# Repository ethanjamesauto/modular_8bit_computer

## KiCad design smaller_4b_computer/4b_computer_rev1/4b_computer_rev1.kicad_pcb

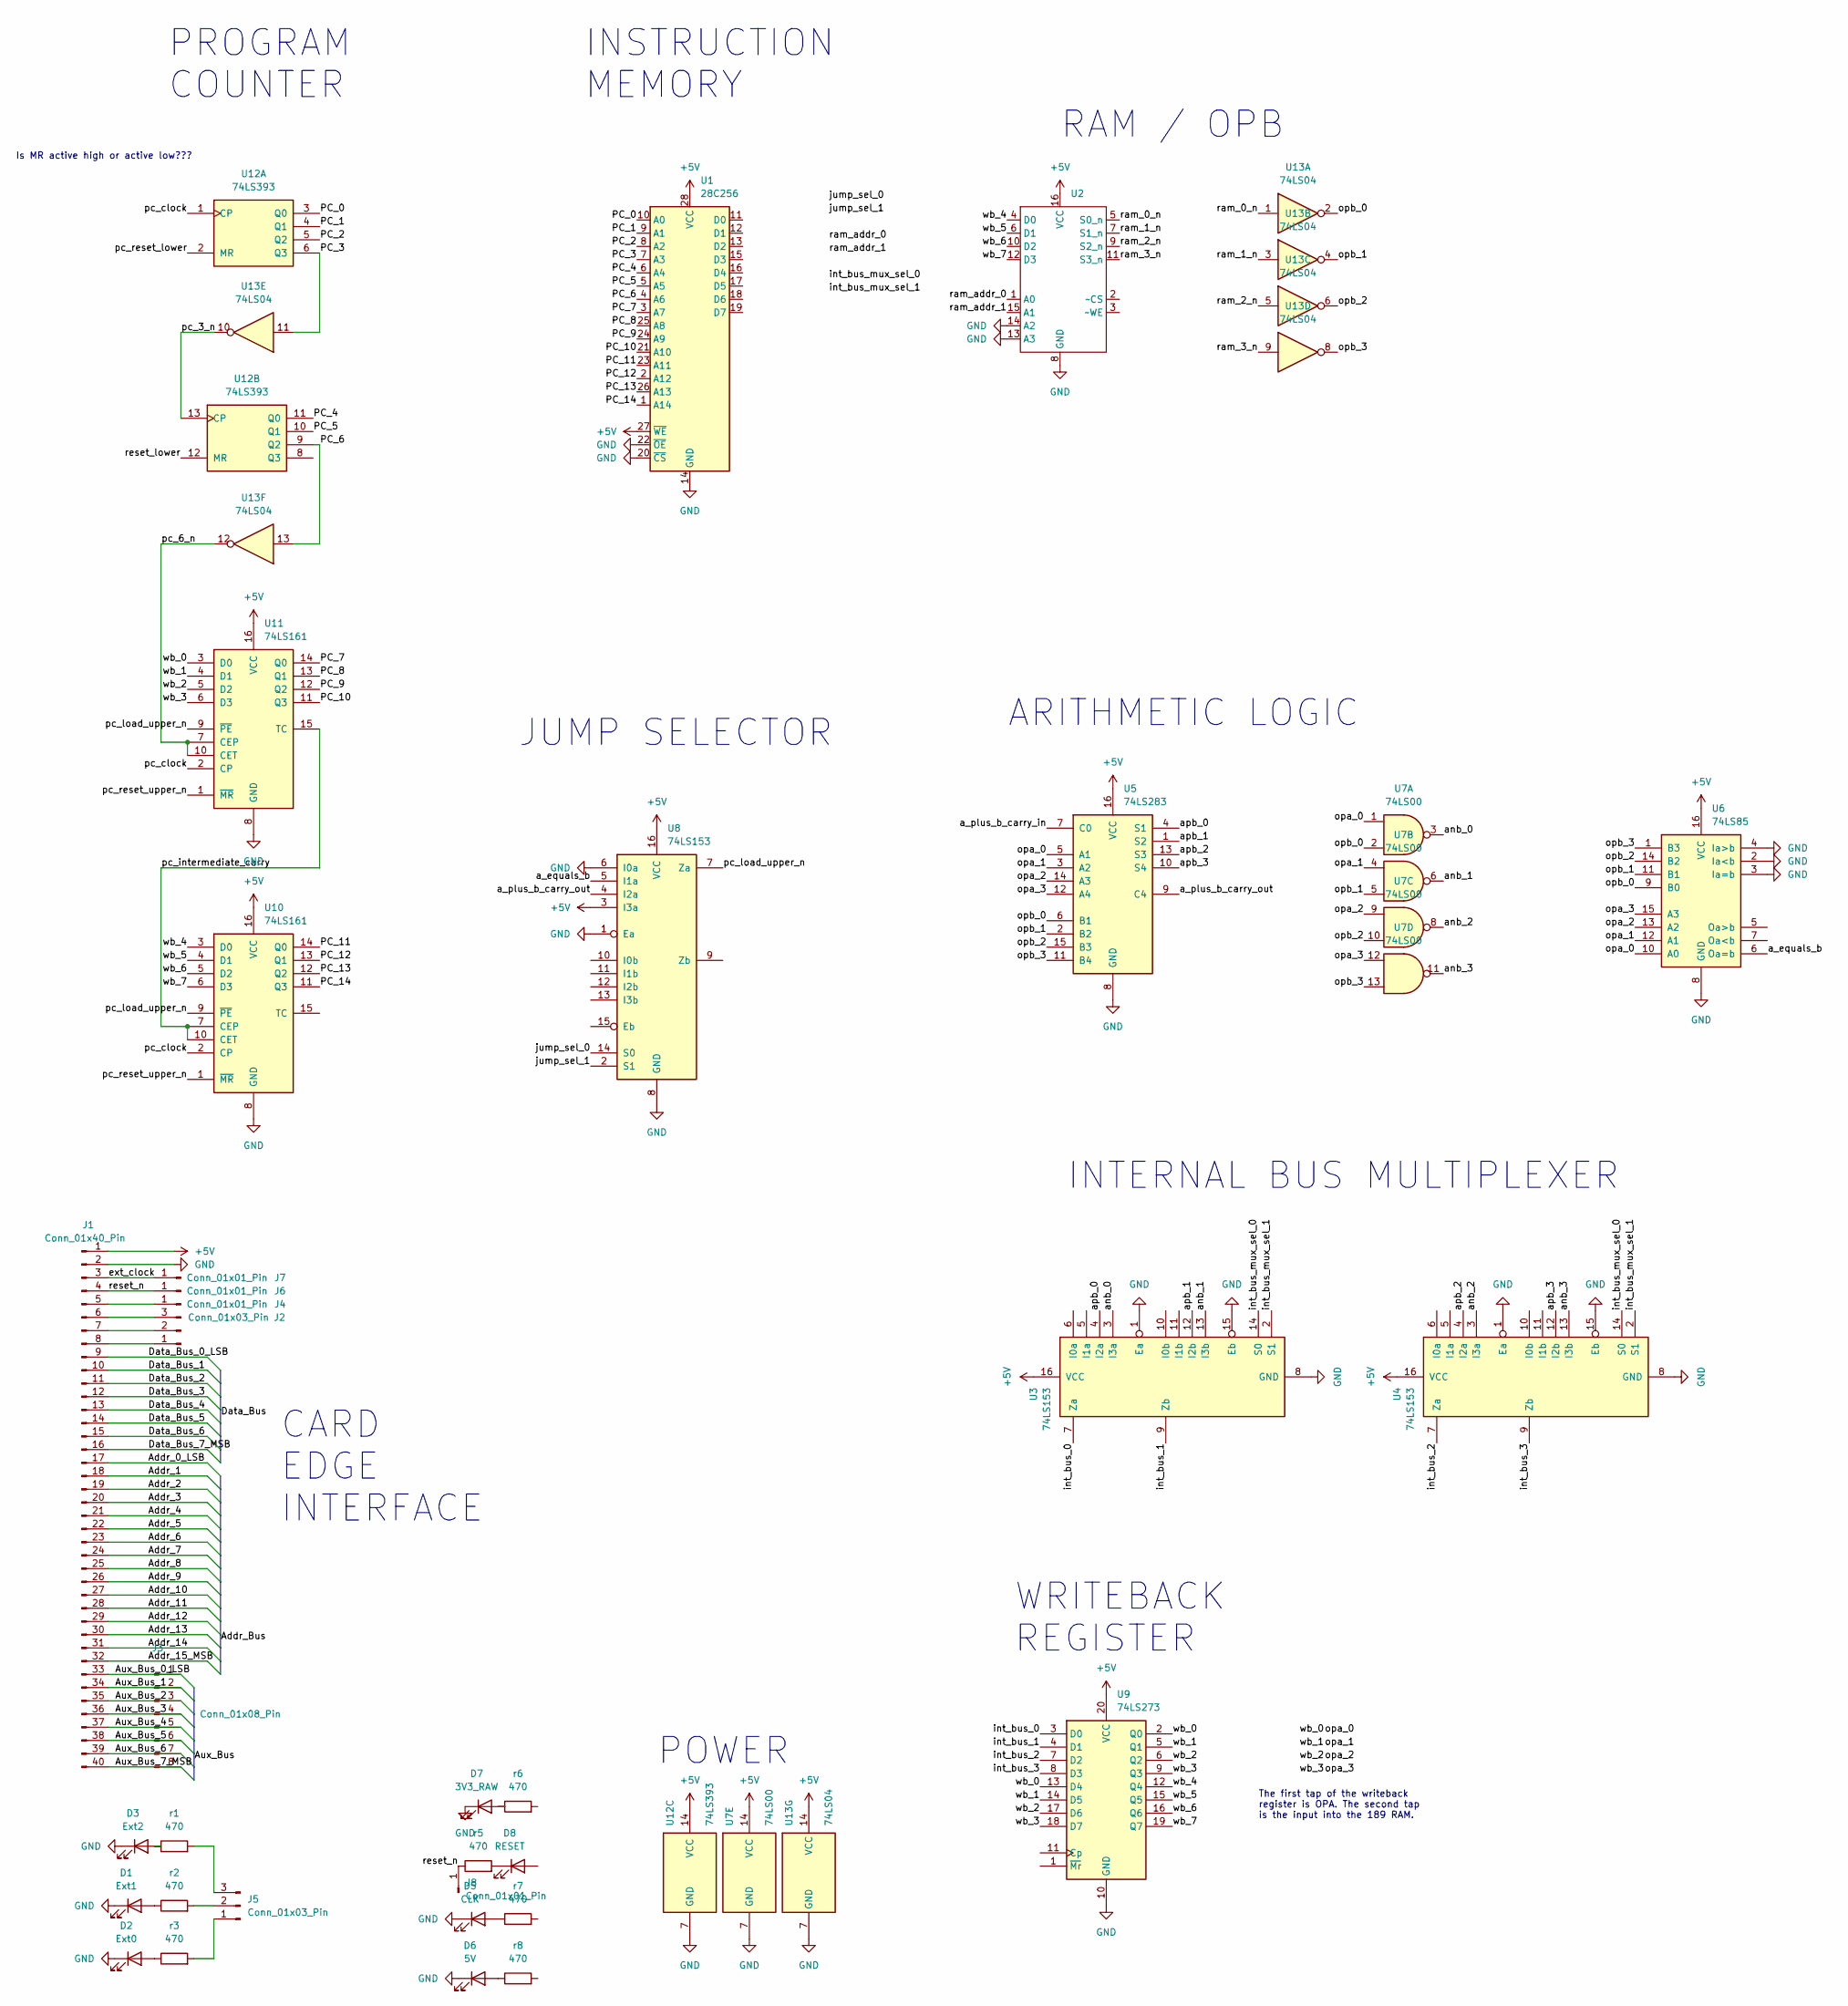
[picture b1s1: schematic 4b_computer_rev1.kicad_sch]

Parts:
D1: Ext1; LED_0603_1608Metric_Pad1.05x0.95mm_HandSolder
D2: Ext0; LED_0603_1608Metric_Pad1.05x0.95mm_HandSolder
D3: Ext2; LED_0603_1608Metric_Pad1.05x0.95mm_HandSolder
D5: CLK; LED_0603_1608Metric_Pad1.05x0.95mm_HandSolder
D6: 5V; LED_0603_1608Metric_Pad1.05x0.95mm_HandSolder
D7: 3V3_RAW; LED_0603_1608Metric_Pad1.05x0.95mm_HandSolder
D8: RESET; LED_0603_1608Metric_Pad1.05x0.95mm_HandSolder
J1: Conn_01x40_Pin; PinHeader_1x40_P2.54mm_Horizontal
J2, J5: Conn_01x03_Pin; PinHeader_1x03_P2.54mm_Vertical
J3: Conn_01x08_Pin; PinHeader_1x08_P2.54mm_Vertical
J4, J6, J7, J8: Conn_01x01_Pin; PinHeader_1x01_P2.54mm_Vertical
U1: 28C256; DIP-28_W15.24mm
U2: DIP-16_W7.62mm
U3, U4, U8: 74LS153; DIP-16_W7.62mm
U5: 74LS283; DIP-16_W7.62mm
U6: 74LS85; DIP-16_W7.62mm
U7: 74LS00; DIP-14_W7.62mm
U9: 74LS273; DIP-20_W7.62mm
U10, U11: 74LS161; DIP-16_W7.62mm
U12: 74LS393; DIP-16_W7.62mm
U13: 74LS04; DIP-14_W7.62mm
r1, r2, r3, r5, r6, r7, r8: 470; R_0603_1608Metric_Pad0.98x0.95mm_HandSolder

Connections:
+5V: J1.1, U1.27 (~WE), U1.28 (VCC), U2.16 (VCC), U3.16 (VCC), U4.16 (VCC), U5.16 (VCC), U6.16 (VCC), U7.14 (VCC), U8.3 (I3a), U8.16 (VCC), U9.20 (VCC), U10.16 (VCC), U11.16 (VCC), U12.14 (VCC), U13.14 (VCC)
/Addr_0_LSB: J1.17
/Addr_1: J1.18
/Addr_2: J1.19
/Addr_3: J1.20
/Addr_4: J1.21
/Addr_5: J1.22
/Addr_6: J1.23
/Addr_7: J1.24
/Addr_8: J1.25
/Addr_9: J1.26
/Addr_10: J1.27
/Addr_11: J1.28
/Addr_12: J1.29
/Addr_13: J1.30
/Addr_14: J1.31
/Addr_15_MSB: J1.32
/Aux_Bus_0_LSB: J1.33, J3.1
/Aux_Bus_1: J1.34, J3.2
/Aux_Bus_2: J1.35, J3.3
/Aux_Bus_3: J1.36, J3.4
/Aux_Bus_4: J1.37, J3.5
/Aux_Bus_5: J1.38, J3.6
/Aux_Bus_6: J1.39, J3.7
/Aux_Bus_7_MSB: J1.40, J3.8
/Data_Bus_0_LSB: J1.9
/Data_Bus_1: J1.10
/Data_Bus_2: J1.11
/Data_Bus_3: J1.12
/Data_Bus_4: J1.13
/Data_Bus_5: J1.14
/Data_Bus_6: J1.15
/Data_Bus_7_MSB: J1.16
/PC_0: U1.10 (A0), U12.3 (Q0)
/PC_1: U1.9 (A1), U12.4 (Q1)
/PC_2: U1.8 (A2), U12.5 (Q2)
/PC_3: U1.7 (A3), U12.6 (Q3), U13.11
/PC_4: U1.6 (A4), U12.11 (Q0)
/PC_5: U1.5 (A5), U12.10 (Q1)
/PC_6: U1.4 (A6), U12.9 (Q2), U13.13
/PC_7: U1.3 (A7), U11.14 (Q0)
/PC_8: U1.25 (A8), U11.13 (Q1)
/PC_9: U1.24 (A9), U11.12 (Q2)
/PC_10: U1.21 (A10), U11.11 (Q3)
/PC_11: U1.23 (A11), U10.14 (Q0)
/PC_12: U1.2 (A12), U10.13 (Q1)
/PC_13: U1.26 (A13), U10.12 (Q2)
/PC_14: U1.1 (A14), U10.11 (Q3)
/a_equals_b: U6.6 (Oa=b), U8.5 (I1a)
/a_plus_b_carry_in: U5.7 (C0)
/a_plus_b_carry_out: U5.9 (C4), U8.4 (I2a)
/anb_0: U3.3 (I3a), U7.3
/anb_1: U3.13 (I3b), U7.6
/anb_2: U4.3 (I3a), U7.8
/anb_3: U4.13 (I3b), U7.11
/apb_0: U3.4 (I2a), U5.4 (S1)
/apb_1: U3.12 (I2b), U5.1 (S2)
/apb_2: U4.4 (I2a), U5.13 (S3)
/apb_3: U4.12 (I2b), U5.10 (S4)
/ext_clock: J1.3, J7.1
/int_bus_0: U3.7 (Za), U9.3 (D0)
/int_bus_1: U3.9 (Zb), U9.4 (D1)
/int_bus_2: U4.7 (Za), U9.7 (D2)
/int_bus_3: U4.9 (Zb), U9.8 (D3)
/int_bus_mux_sel_0: U3.14 (S0), U4.14 (S0)
/int_bus_mux_sel_1: U3.2 (S1), U4.2 (S1)
/jump_sel_0: U8.14 (S0)
/jump_sel_1: U8.2 (S1)
/opa_0: U5.5 (A1), U6.10 (A0), U7.1, U9.2 (Q0), U9.13 (D4), U11.3 (D0)
/opa_1: U5.3 (A2), U6.12 (A1), U7.4, U9.5 (Q1), U9.14 (D5), U11.4 (D1)
/opa_2: U5.14 (A3), U6.13 (A2), U7.9, U9.6 (Q2), U9.17 (D6), U11.5 (D2)
/opa_3: U5.12 (A4), U6.15 (A3), U7.12, U9.9 (Q3), U9.18 (D7), U11.6 (D3)
/opb_0: U5.6 (B1), U6.9 (B0), U7.2, U13.2
/opb_1: U5.2 (B2), U6.11 (B1), U7.5, U13.4
/opb_2: U5.15 (B3), U6.14 (B2), U7.10, U13.6
/opb_3: U5.11 (B4), U6.1 (B3), U7.13, U13.8
/pc_3_n: U12.13 (CP), U13.10
/pc_6_n: U11.7 (CEP), U11.10 (CET), U13.12
/pc_clock: U10.2 (CP), U11.2 (CP), U12.1 (CP)
/pc_intermediate_carry: U10.7 (CEP), U10.10 (CET), U11.15 (TC)
/pc_load_upper_n: U8.7 (Za), U10.9 (~PE), U11.9 (~PE)
/pc_reset_lower: U12.2 (MR)
/pc_reset_upper_n: U10.1 (~MR), U11.1 (~MR)
/ram_0_n: U2.5 (S0_n), U13.1
/ram_1_n: U2.7 (S1_n), U13.3
/ram_2_n: U2.9 (S2_n), U13.5
/ram_3_n: U2.11 (S3_n), U13.9
/ram_addr_0: U2.1 (A0)
/ram_addr_1: U2.15 (A1)
/reset_lower: U12.12 (MR)
/reset_n: J1.4, J6.1, J8.1, r5.1
/wb_4: U2.4 (D0), U9.12 (Q4), U10.3 (D0)
/wb_5: U2.6 (D1), U9.15 (Q5), U10.4 (D1)
/wb_6: U2.10 (D2), U9.16 (Q6), U10.5 (D2)
/wb_7: U2.12 (D3), U9.19 (Q7), U10.6 (D3)
GND: D1.1 (K), D2.1 (K), D3.1 (K), D5.1 (K), D6.1 (K), D7.1 (K), J1.2, U1.14 (GND), U1.20 (~CS), U1.22 (~OE), U2.8 (GND), U2.13 (A3), U2.14 (A2), U3.1 (Ea), U3.8 (GND), U3.15 (Eb), U4.1 (Ea), U4.8 (GND), U4.15 (Eb), U5.8 (GND), U6.2 (Ia<b), U6.3 (Ia=b), U6.4 (Ia>b), U6.8 (GND), U7.7 (GND), U8.1 (Ea), U8.6 (I0a), U8.8 (GND), U9.10 (GND), U10.8 (GND), U11.8 (GND), U12.7 (GND), U13.7 (GND)
unnamed: D1.2 (A), r2.1
unnamed: D2.2 (A), r3.1
unnamed: D3.2 (A), r1.1
unnamed: D5.2 (A), r7.1
unnamed: D6.2 (A), r8.1
unnamed: D7.2 (A), r6.1
unnamed: D8.1 (K), r5.2
unnamed: J1.5, J4.1
unnamed: J1.6, J2.3
unnamed: J1.7, J2.2
unnamed: J1.8, J2.1
unnamed: J5.1, r3.2
unnamed: J5.2, r2.2
unnamed: J5.3, r1.2

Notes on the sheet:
PROGRAM COUNTER
INTERNAL BUS MULTIPLEXER
RAM / OPB
JUMP SELECTOR
CARD EDGE INTERFACE
WRITEBACK REGISTER
POWER
Is MR active high or active low???
ARITHMETIC LOGIC
INSTRUCTION MEMORY
The first tap of the writeback register is OPA. The second tap is the input into the 189 RAM.

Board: 2 copper layers, 35 parts (0 on the bottom side), 79 nets, no tracks yet.

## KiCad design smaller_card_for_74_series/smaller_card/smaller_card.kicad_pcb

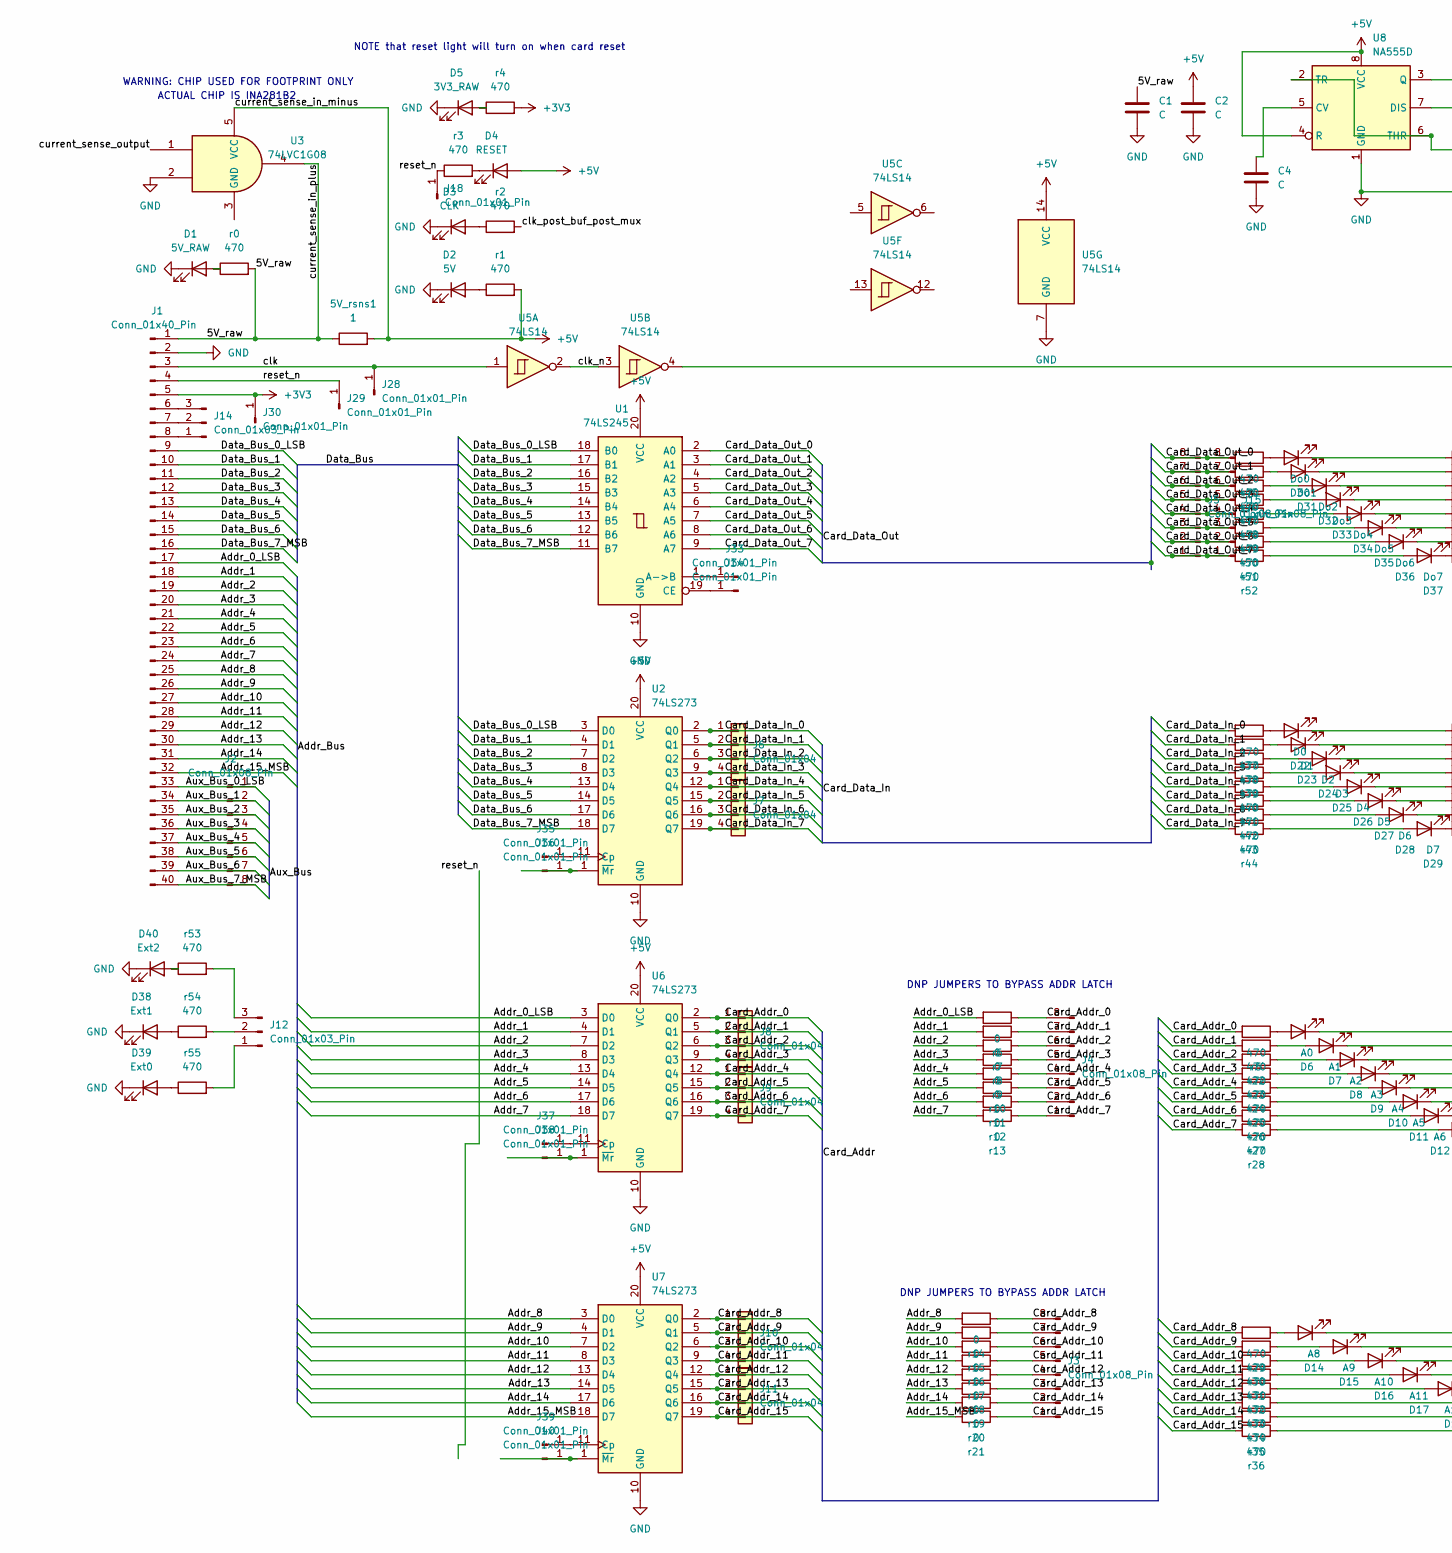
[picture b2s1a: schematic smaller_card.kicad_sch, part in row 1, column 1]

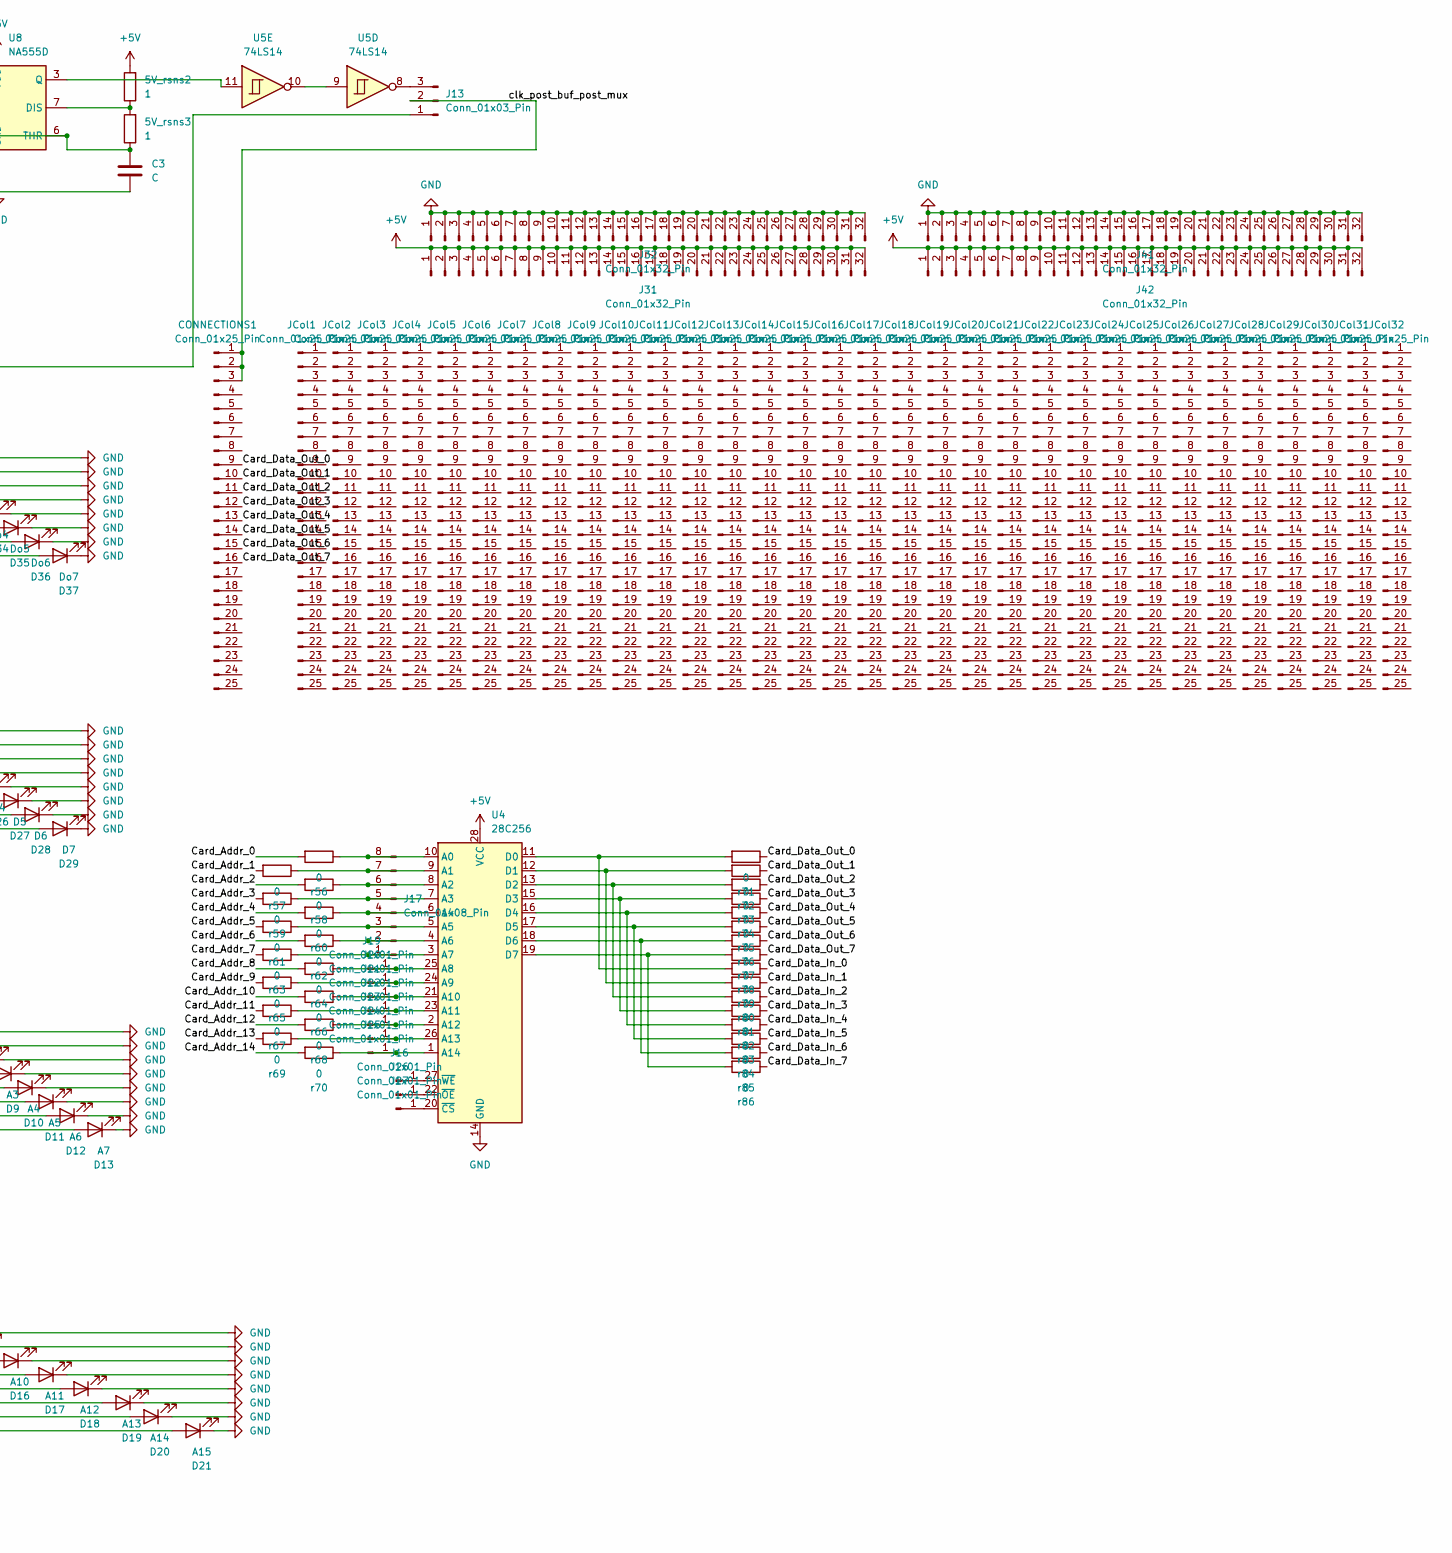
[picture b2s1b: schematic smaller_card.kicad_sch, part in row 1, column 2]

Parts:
5V_rsns1, 5V_rsns2, 5V_rsns3: 1; R_1206_3216Metric
C1, C2, C3, C4: C; C_1206_3216Metric
CONNECTIONS1: Conn_01x25_Pin; PinHeader_1x25_P2.54mm_Vertical
D1: 5V_RAW; LED_0603_1608Metric_Pad1.05x0.95mm_HandSolder
D2: 5V; LED_0603_1608Metric_Pad1.05x0.95mm_HandSolder
D3: CLK; LED_0603_1608Metric_Pad1.05x0.95mm_HandSolder
D4: RESET; LED_0603_1608Metric_Pad1.05x0.95mm_HandSolder
D5: 3V3_RAW; LED_0603_1608Metric_Pad1.05x0.95mm_HandSolder
D6: A0; LED_0603_1608Metric_Pad1.05x0.95mm_HandSolder
D7: A1; LED_0603_1608Metric_Pad1.05x0.95mm_HandSolder
D8: A2; LED_0603_1608Metric_Pad1.05x0.95mm_HandSolder
D9: A3; LED_0603_1608Metric_Pad1.05x0.95mm_HandSolder
D10: A4; LED_0603_1608Metric_Pad1.05x0.95mm_HandSolder
D11: A5; LED_0603_1608Metric_Pad1.05x0.95mm_HandSolder
D12: A6; LED_0603_1608Metric_Pad1.05x0.95mm_HandSolder
D13: A7; LED_0603_1608Metric_Pad1.05x0.95mm_HandSolder
D14: A8; LED_0603_1608Metric_Pad1.05x0.95mm_HandSolder
D15: A9; LED_0603_1608Metric_Pad1.05x0.95mm_HandSolder
D16: A10; LED_0603_1608Metric_Pad1.05x0.95mm_HandSolder
D17: A11; LED_0603_1608Metric_Pad1.05x0.95mm_HandSolder
D18: A12; LED_0603_1608Metric_Pad1.05x0.95mm_HandSolder
D19: A13; LED_0603_1608Metric_Pad1.05x0.95mm_HandSolder
D20: A14; LED_0603_1608Metric_Pad1.05x0.95mm_HandSolder
D21: A15; LED_0603_1608Metric_Pad1.05x0.95mm_HandSolder
D22: D0; LED_0603_1608Metric_Pad1.05x0.95mm_HandSolder
D23: D1; LED_0603_1608Metric_Pad1.05x0.95mm_HandSolder
D24: D2; LED_0603_1608Metric_Pad1.05x0.95mm_HandSolder
D25: D3; LED_0603_1608Metric_Pad1.05x0.95mm_HandSolder
D26: D4; LED_0603_1608Metric_Pad1.05x0.95mm_HandSolder
D27: D5; LED_0603_1608Metric_Pad1.05x0.95mm_HandSolder
D28: D6; LED_0603_1608Metric_Pad1.05x0.95mm_HandSolder
D29: D7; LED_0603_1608Metric_Pad1.05x0.95mm_HandSolder
D30: Do0; LED_0603_1608Metric_Pad1.05x0.95mm_HandSolder
D31: Do1; LED_0603_1608Metric_Pad1.05x0.95mm_HandSolder
D32: Do2; LED_0603_1608Metric_Pad1.05x0.95mm_HandSolder
D33: Do3; LED_0603_1608Metric_Pad1.05x0.95mm_HandSolder
D34: Do4; LED_0603_1608Metric_Pad1.05x0.95mm_HandSolder
D35: Do5; LED_0603_1608Metric_Pad1.05x0.95mm_HandSolder
D36: Do6; LED_0603_1608Metric_Pad1.05x0.95mm_HandSolder
D37: Do7; LED_0603_1608Metric_Pad1.05x0.95mm_HandSolder
D38: Ext1; LED_0603_1608Metric_Pad1.05x0.95mm_HandSolder
D39: Ext0; LED_0603_1608Metric_Pad1.05x0.95mm_HandSolder
D40: Ext2; LED_0603_1608Metric_Pad1.05x0.95mm_HandSolder
J1: Conn_01x40_Pin; PinHeader_1x40_P2.54mm_Horizontal
J2, J3, J4, J5, J15, J17: Conn_01x08_Pin; PinHeader_1x08_P2.54mm_Vertical
J6, J7, J8, J9, J10, J11: Conn_01x04; PinHeader_1x04_P2.54mm_Vertical
J12, J13, J14: Conn_01x03_Pin; PinHeader_1x03_P2.54mm_Vertical
J16, J18, J19, J20, J21, J22, J23, J24, J25, J26, J27, J28, J29, J30, J33, J34, J35, J36, J37, J38, J39, J40: Conn_01x01_Pin; PinHeader_1x01_P2.54mm_Vertical
J31, J32, J41, J42: Conn_01x32_Pin; PinHeader_1x32_P2.54mm_Vertical
JCol1, JCol2, JCol3, JCol4, JCol5, JCol6, JCol7, JCol8, JCol9, JCol10, JCol11, JCol12, JCol13, JCol14, JCol15, JCol16, JCol17, JCol18, JCol19, JCol20, JCol21, JCol22, JCol23, JCol24, JCol25, JCol26, JCol27, JCol28, JCol29, JCol30, JCol31, JCol32: Conn_01x25_Pin; PinHeader_1x25_P2.54mm_Vertical
U1: 74LS245; DIP-20_W7.62mm_Socket
U2, U6, U7: 74LS273; DIP-20_W7.62mm_Socket
U3: 74LVC1G08; SOT-23-6_Handsoldering
U4: 28C256; DIP-28_W15.24mm
U5: 74LS14; DIP-14_W7.62mm_Socket
U8: NA555D; DIP-8_W7.62mm_Socket
r0, r1, r2, r3, r4, r5, r22, r23, r24, r25, r26, r27, r28, r29, r30, r31, r32, r33, r34, r35, r36, r37, r38, r39, r40, r41, r42, r43, r44, r45, r46, r47, r48, r49, r50, r51, r52, r53, r54, r55: 470; R_0603_1608Metric_Pad0.98x0.95mm_HandSolder
r6, r7, r8, r9, r10, r11, r12, r13, r14, r15, r16, r17, r18, r19, r20, r21, r56, r57, r58, r59, r60, r61, r62, r63, r64, r65, r66, r67, r68, r69, r70, r71, r72, r73, r74, r75, r76, r77, r78, r79, r80, r81, r82, r83, r84, r85, r86: 0; R_0603_1608Metric_Pad0.98x0.95mm_HandSolder

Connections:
+3V3: J1.5, J30.1, r4.2; also elsewhere on the board
+5V: 5V_rsns1.2, 5V_rsns2.2, C2.1, D4.2 (A), J31.1, J31.2, J31.3, J31.4, J31.5, J31.6, J31.7, J31.8, J31.9, J31.10, J31.11, J31.12, J31.13, J31.14, J31.15, J31.16, J31.17, J31.18, J31.19, J31.20, J31.21, J31.22, J31.23, J31.24, J31.25, J31.26, J31.27, J31.28, J31.29, J31.30, J31.31, J31.32, J42.1, J42.2, J42.3, J42.4, J42.5, J42.6, J42.7, J42.8, J42.9, J42.10, J42.11, J42.12, J42.13, J42.14, J42.15, J42.16, J42.17, J42.18, J42.19, J42.20, J42.21, J42.22, J42.23, J42.24, J42.25, J42.26, J42.27, J42.28, J42.29, J42.30, J42.31, J42.32, U1.20 (VCC), U2.20 (VCC), U3.3 (GND), U3.5 (VCC), U3.6, U4.28 (VCC), U5.14 (VCC), U6.20 (VCC), U7.20 (VCC), U8.4 (R), U8.8 (VCC), r1.2; also elsewhere on the board
/5V_raw: 5V_rsns1.1, C1.1, J1.1, U3.4, r0.2
/Addr_0_LSB: J1.17, U6.3 (D0), r6.2
/Addr_1: J1.18, U6.4 (D1), r7.2
/Addr_2: J1.19, U6.7 (D2), r8.2
/Addr_3: J1.20, U6.8 (D3), r9.2
/Addr_4: J1.21, U6.13 (D4), r10.2
/Addr_5: J1.22, U6.14 (D5), r11.2
/Addr_6: J1.23, U6.17 (D6), r12.2
/Addr_7: J1.24, U6.18 (D7), r13.2
/Addr_8: J1.25, U7.3 (D0), r14.2
/Addr_9: J1.26, U7.4 (D1), r15.2
/Addr_10: J1.27, U7.7 (D2), r16.2
/Addr_11: J1.28, U7.8 (D3), r17.2
/Addr_12: J1.29, U7.13 (D4), r18.2
/Addr_13: J1.30, U7.14 (D5), r19.2
/Addr_14: J1.31, U7.17 (D6), r20.2
/Addr_15_MSB: J1.32, U7.18 (D7), r21.2
/Aux_Bus_0_LSB: J1.33, J2.1
/Aux_Bus_1: J1.34, J2.2
/Aux_Bus_2: J1.35, J2.3
/Aux_Bus_3: J1.36, J2.4
/Aux_Bus_4: J1.37, J2.5
/Aux_Bus_5: J1.38, J2.6
/Aux_Bus_6: J1.39, J2.7
/Aux_Bus_7_MSB: J1.40, J2.8
/Card_Addr_0: J4.8, J8.1, U6.2 (Q0), r5.2, r6.1, r56.2
/Card_Addr_1: J4.7, J8.2, U6.5 (Q1), r7.1, r22.2, r57.2
/Card_Addr_2: J4.6, J8.3, U6.6 (Q2), r8.1, r23.2, r58.2
/Card_Addr_3: J4.5, J8.4, U6.9 (Q3), r9.1, r24.2, r59.2
/Card_Addr_4: J4.4, J9.1, U6.12 (Q4), r10.1, r25.2, r60.2
/Card_Addr_5: J4.3, J9.2, U6.15 (Q5), r11.1, r26.2, r61.2
/Card_Addr_6: J4.2, J9.3, U6.16 (Q6), r12.1, r27.2, r62.2
/Card_Addr_7: J4.1, J9.4, U6.19 (Q7), r13.1, r28.2, r63.2
/Card_Addr_8: J3.8, J10.1, U7.2 (Q0), r14.1, r29.2, r64.2
/Card_Addr_9: J3.7, J10.2, U7.5 (Q1), r15.1, r30.2, r65.2
/Card_Addr_10: J3.6, J10.3, U7.6 (Q2), r16.1, r31.2, r66.2
/Card_Addr_11: J3.5, J10.4, U7.9 (Q3), r17.1, r32.2, r67.2
/Card_Addr_12: J3.4, J11.1, U7.12 (Q4), r18.1, r33.2, r68.2
/Card_Addr_13: J3.3, J11.2, U7.15 (Q5), r19.1, r34.2, r69.2
/Card_Addr_14: J3.2, J11.3, U7.16 (Q6), r20.1, r35.2, r70.2
/Card_Addr_15: J3.1, J11.4, U7.19 (Q7), r21.1, r36.2
/Card_Data_In_0: J6.1, U2.2 (Q0), r37.2, r79.1
/Card_Data_In_1: J6.2, U2.5 (Q1), r38.2, r80.1
/Card_Data_In_2: J6.3, U2.6 (Q2), r39.2, r81.1
/Card_Data_In_3: J6.4, U2.9 (Q3), r40.2, r82.1
/Card_Data_In_4: J7.1, U2.12 (Q4), r41.2, r83.1
/Card_Data_In_5: J7.2, U2.15 (Q5), r42.2, r84.1
/Card_Data_In_6: J7.3, U2.16 (Q6), r43.2, r85.1
/Card_Data_In_7: J7.4, U2.19 (Q7), r44.2, r86.1
/Card_Data_Out_0: CONNECTIONS1.9, J5.8, J15.8, U1.2 (A0), r45.2, r71.1
/Card_Data_Out_1: CONNECTIONS1.10, J5.7, J15.7, U1.3 (A1), r46.2, r72.1
/Card_Data_Out_2: CONNECTIONS1.11, J5.6, J15.6, U1.4 (A2), r47.2, r73.1
/Card_Data_Out_3: CONNECTIONS1.12, J5.5, J15.5, U1.5 (A3), r48.2, r74.1
/Card_Data_Out_4: CONNECTIONS1.13, J5.4, J15.4, U1.6 (A4), r49.2, r75.1
/Card_Data_Out_5: CONNECTIONS1.14, J5.3, J15.3, U1.7 (A5), r50.2, r76.1
/Card_Data_Out_6: CONNECTIONS1.15, J5.2, J15.2, U1.8 (A6), r51.2, r77.1
/Card_Data_Out_7: CONNECTIONS1.16, J5.1, J15.1, U1.9 (A7), r52.2, r78.1
/Data_Bus_0_LSB: J1.9, U1.18 (B0), U2.3 (D0)
/Data_Bus_1: J1.10, U1.17 (B1), U2.4 (D1)
/Data_Bus_2: J1.11, U1.16 (B2), U2.7 (D2)
/Data_Bus_3: J1.12, U1.15 (B3), U2.8 (D3)
/Data_Bus_4: J1.13, U1.14 (B4), U2.13 (D4)
/Data_Bus_5: J1.14, U1.13 (B5), U2.14 (D5)
/Data_Bus_6: J1.15, U1.12 (B6), U2.17 (D6)
/Data_Bus_7_MSB: J1.16, U1.11 (B7), U2.18 (D7)
/clk: J1.3, J28.1, U5.1
/clk_n: U5.2, U5.3
/clk_post_buf_post_mux: CONNECTIONS1.1, CONNECTIONS1.2, CONNECTIONS1.3, J13.2, r2.2
GND: C1.2, C2.2, C3.2, C4.2, D1.1 (K), D2.1 (K), D3.1 (K), D5.1 (K), D6.1 (K), D7.1 (K), D8.1 (K), D9.1 (K), D10.1 (K), D11.1 (K), D12.1 (K), D13.1 (K), D14.1 (K), D15.1 (K), D16.1 (K), D17.1 (K), D18.1 (K), D19.1 (K), D20.1 (K), D21.1 (K), D22.1 (K), D23.1 (K), D24.1 (K), D25.1 (K), D26.1 (K), D27.1 (K), D28.1 (K), D29.1 (K), D30.1 (K), D31.1 (K), D32.1 (K), D33.1 (K), D34.1 (K), D35.1 (K), D36.1 (K), D37.1 (K), D38.1 (K), D39.1 (K), D40.1 (K), J1.2, J32.1, J32.2, J32.3, J32.4, J32.5, J32.6, J32.7, J32.8, J32.9, J32.10, J32.11, J32.12, J32.13, J32.14, J32.15, J32.16, J32.17, J32.18, J32.19, J32.20, J32.21, J32.22, J32.23, J32.24, J32.25, J32.26, J32.27, J32.28, J32.29, J32.30, J32.31, J32.32, J41.1, J41.2, J41.3, J41.4, J41.5, J41.6, J41.7, J41.8, J41.9, J41.10, J41.11, J41.12, J41.13, J41.14, J41.15, J41.16, J41.17, J41.18, J41.19, J41.20, J41.21, J41.22, J41.23, J41.24, J41.25, J41.26, J41.27, J41.28, J41.29, J41.30, J41.31, J41.32, U1.10 (GND), U2.10 (GND), U3.2, U4.14 (GND), U5.7 (GND), U6.10 (GND), U7.10 (GND), U8.1 (GND); also elsewhere on the board
unnamed: D1.2 (A), r0.1
unnamed: D2.2 (A), r1.1
unnamed: D3.2 (A), r2.1
unnamed: D4.1 (K), r3.2
unnamed: D5.2 (A), r4.1
unnamed: D6.2 (A), r5.1
unnamed: D7.2 (A), r22.1
unnamed: D8.2 (A), r23.1
unnamed: D9.2 (A), r24.1
unnamed: D10.2 (A), r25.1
unnamed: D11.2 (A), r26.1
unnamed: D12.2 (A), r27.1
unnamed: D13.2 (A), r28.1
unnamed: D14.2 (A), r29.1
unnamed: D15.2 (A), r30.1
unnamed: D16.2 (A), r31.1
unnamed: D17.2 (A), r32.1
unnamed: D18.2 (A), r33.1
unnamed: D19.2 (A), r34.1
unnamed: D20.2 (A), r35.1
unnamed: D21.2 (A), r36.1
unnamed: D22.2 (A), r37.1
unnamed: D23.2 (A), r38.1
unnamed: D24.2 (A), r39.1
unnamed: D25.2 (A), r40.1
unnamed: D26.2 (A), r41.1
unnamed: D27.2 (A), r42.1
unnamed: D28.2 (A), r43.1
unnamed: D29.2 (A), r44.1
unnamed: D30.2 (A), r45.1
unnamed: D31.2 (A), r46.1
unnamed: D32.2 (A), r47.1
unnamed: D33.2 (A), r48.1
unnamed: D34.2 (A), r49.1
unnamed: D35.2 (A), r50.1
unnamed: D36.2 (A), r51.1
unnamed: D37.2 (A), r52.1
unnamed: D38.2 (A), r54.1
unnamed: D39.2 (A), r55.1
unnamed: D40.2 (A), r53.1
unnamed: J1.6, J14.3
unnamed: J1.7, J14.2
unnamed: J1.8, J14.1
unnamed: J12.1, r55.2
unnamed: J12.2, r54.2
unnamed: J12.3, r53.2
unnamed: J13.1, U5.4
unnamed: J13.3, U5.8
unnamed: J16.1, U4.27 (~WE)
unnamed: J17.1, U4.3 (A7), r63.1
unnamed: J17.2, U4.4 (A6), r62.1
unnamed: J17.3, U4.5 (A5), r61.1
unnamed: J17.4, U4.6 (A4), r60.1
unnamed: J17.5, U4.7 (A3), r59.1
unnamed: J17.6, U4.8 (A2), r58.1
unnamed: J17.7, U4.9 (A1), r57.1
unnamed: J17.8, U4.10 (A0), r56.1
unnamed: J19.1, U4.25 (A8), r64.1
unnamed: J20.1, U4.24 (A9), r65.1
unnamed: J21.1, U4.21 (A10), r66.1
unnamed: J22.1, U4.23 (A11), r67.1
unnamed: J23.1, U4.2 (A12), r68.1
unnamed: J24.1, U4.26 (A13), r69.1
unnamed: J25.1, U4.1 (A14), r70.1
unnamed: J26.1, U4.22 (~OE)
unnamed: J27.1, U4.20 (~CS)
unnamed: J33.1, U1.1 (A->B)
unnamed: J34.1, U1.19 (CE)
unnamed: J35.1, U2.11 (Cp)
unnamed: J36.1, U2.1 (~Mr)
unnamed: J37.1, U6.11 (Cp)
unnamed: J38.1, U6.1 (~Mr)
unnamed: J39.1, U7.11 (Cp)
unnamed: J40.1, U7.1 (~Mr)
unnamed: U4.11 (D0), r71.2, r79.2
unnamed: U4.12 (D1), r72.2, r80.2
unnamed: U4.13 (D2), r73.2, r81.2
unnamed: U4.15 (D3), r74.2, r82.2
unnamed: U4.16 (D4), r75.2, r83.2
unnamed: U4.17 (D5), r76.2, r84.2
unnamed: U4.18 (D6), r77.2, r85.2
unnamed: U4.19 (D7), r78.2, r86.2
unnamed: U5.9, U5.10
unnamed: C4.1, U8.5 (CV)
unnamed: 5V_rsns2.1, 5V_rsns3.2, U8.7 (DIS)
unnamed: U5.11, U8.3 (Q)
unnamed: 5V_rsns3.1, C3.1, U8.2 (TR), U8.6 (THR)

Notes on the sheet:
NOTE that reset light will turn on when card reset
DNP JUMPERS TO BYPASS ADDR LATCH
WARNING: CHIP USED FOR FOOTPRINT ONLY
ACTUAL CHIP IS INA281B2

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
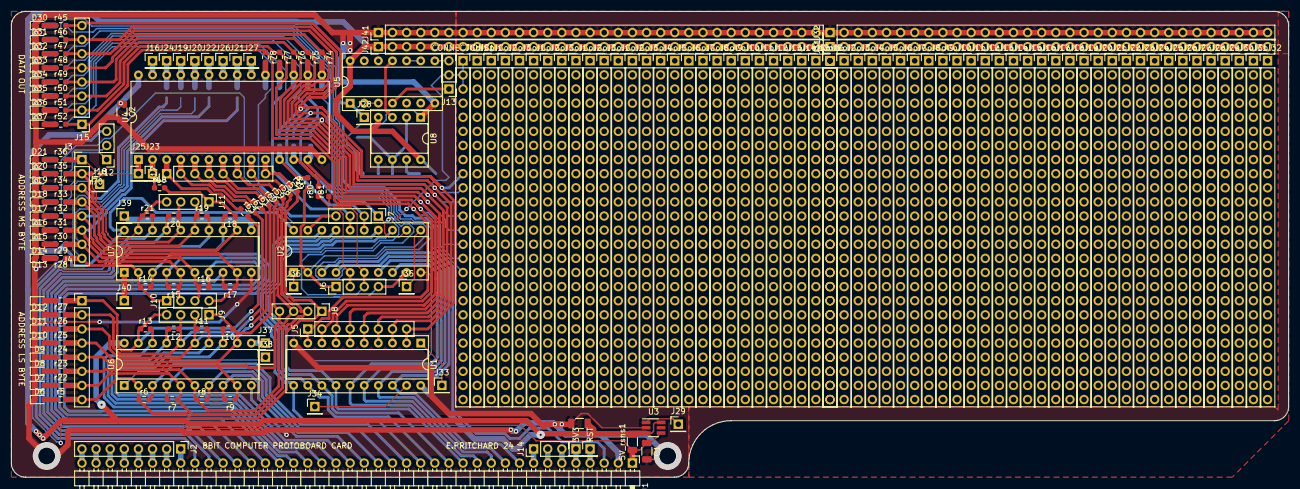
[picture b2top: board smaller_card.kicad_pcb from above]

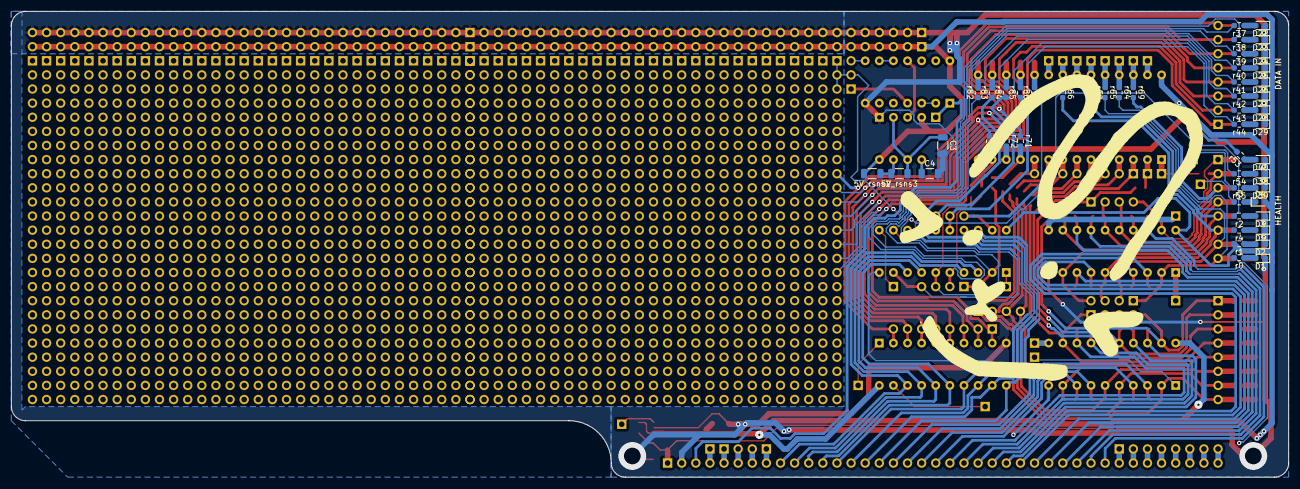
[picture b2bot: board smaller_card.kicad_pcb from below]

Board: 2 copper layers, 229.9 x 83.8 mm, 245 parts (49 on the bottom side), 160 nets.

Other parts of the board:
3V3: Conn_01x01_Pin; PinHeader_1x01_P2.54mm_Vertical
C2#2: C; C_1206_3216Metric
JCol1#2, JCol1#3, JCol1#4, JCol1#5, JCol1#6, JCol2#2, JCol2#3, JCol2#4, JCol2#5, JCol3#2, JCol3#3, JCol3#4, JCol3#5, JCol4#2, JCol5#2, JCol6#2, JCol7#2, JCol8#2, JCol9#2, JCol10#2, JCol11#2, JCol12#2, JCol13#2, JCol14#2, JCol15#2, JCol16#2: Conn_01x25_Pin; PinHeader_1x25_P2.54mm_Vertical
RST: Conn_01x01_Pin; PinHeader_1x01_P2.54mm_Vertical

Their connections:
+3V3: 3V3.1; also elsewhere on the board
+5V: C2#2.1; also elsewhere on the board
GND: C2#2.2; also elsewhere on the board
